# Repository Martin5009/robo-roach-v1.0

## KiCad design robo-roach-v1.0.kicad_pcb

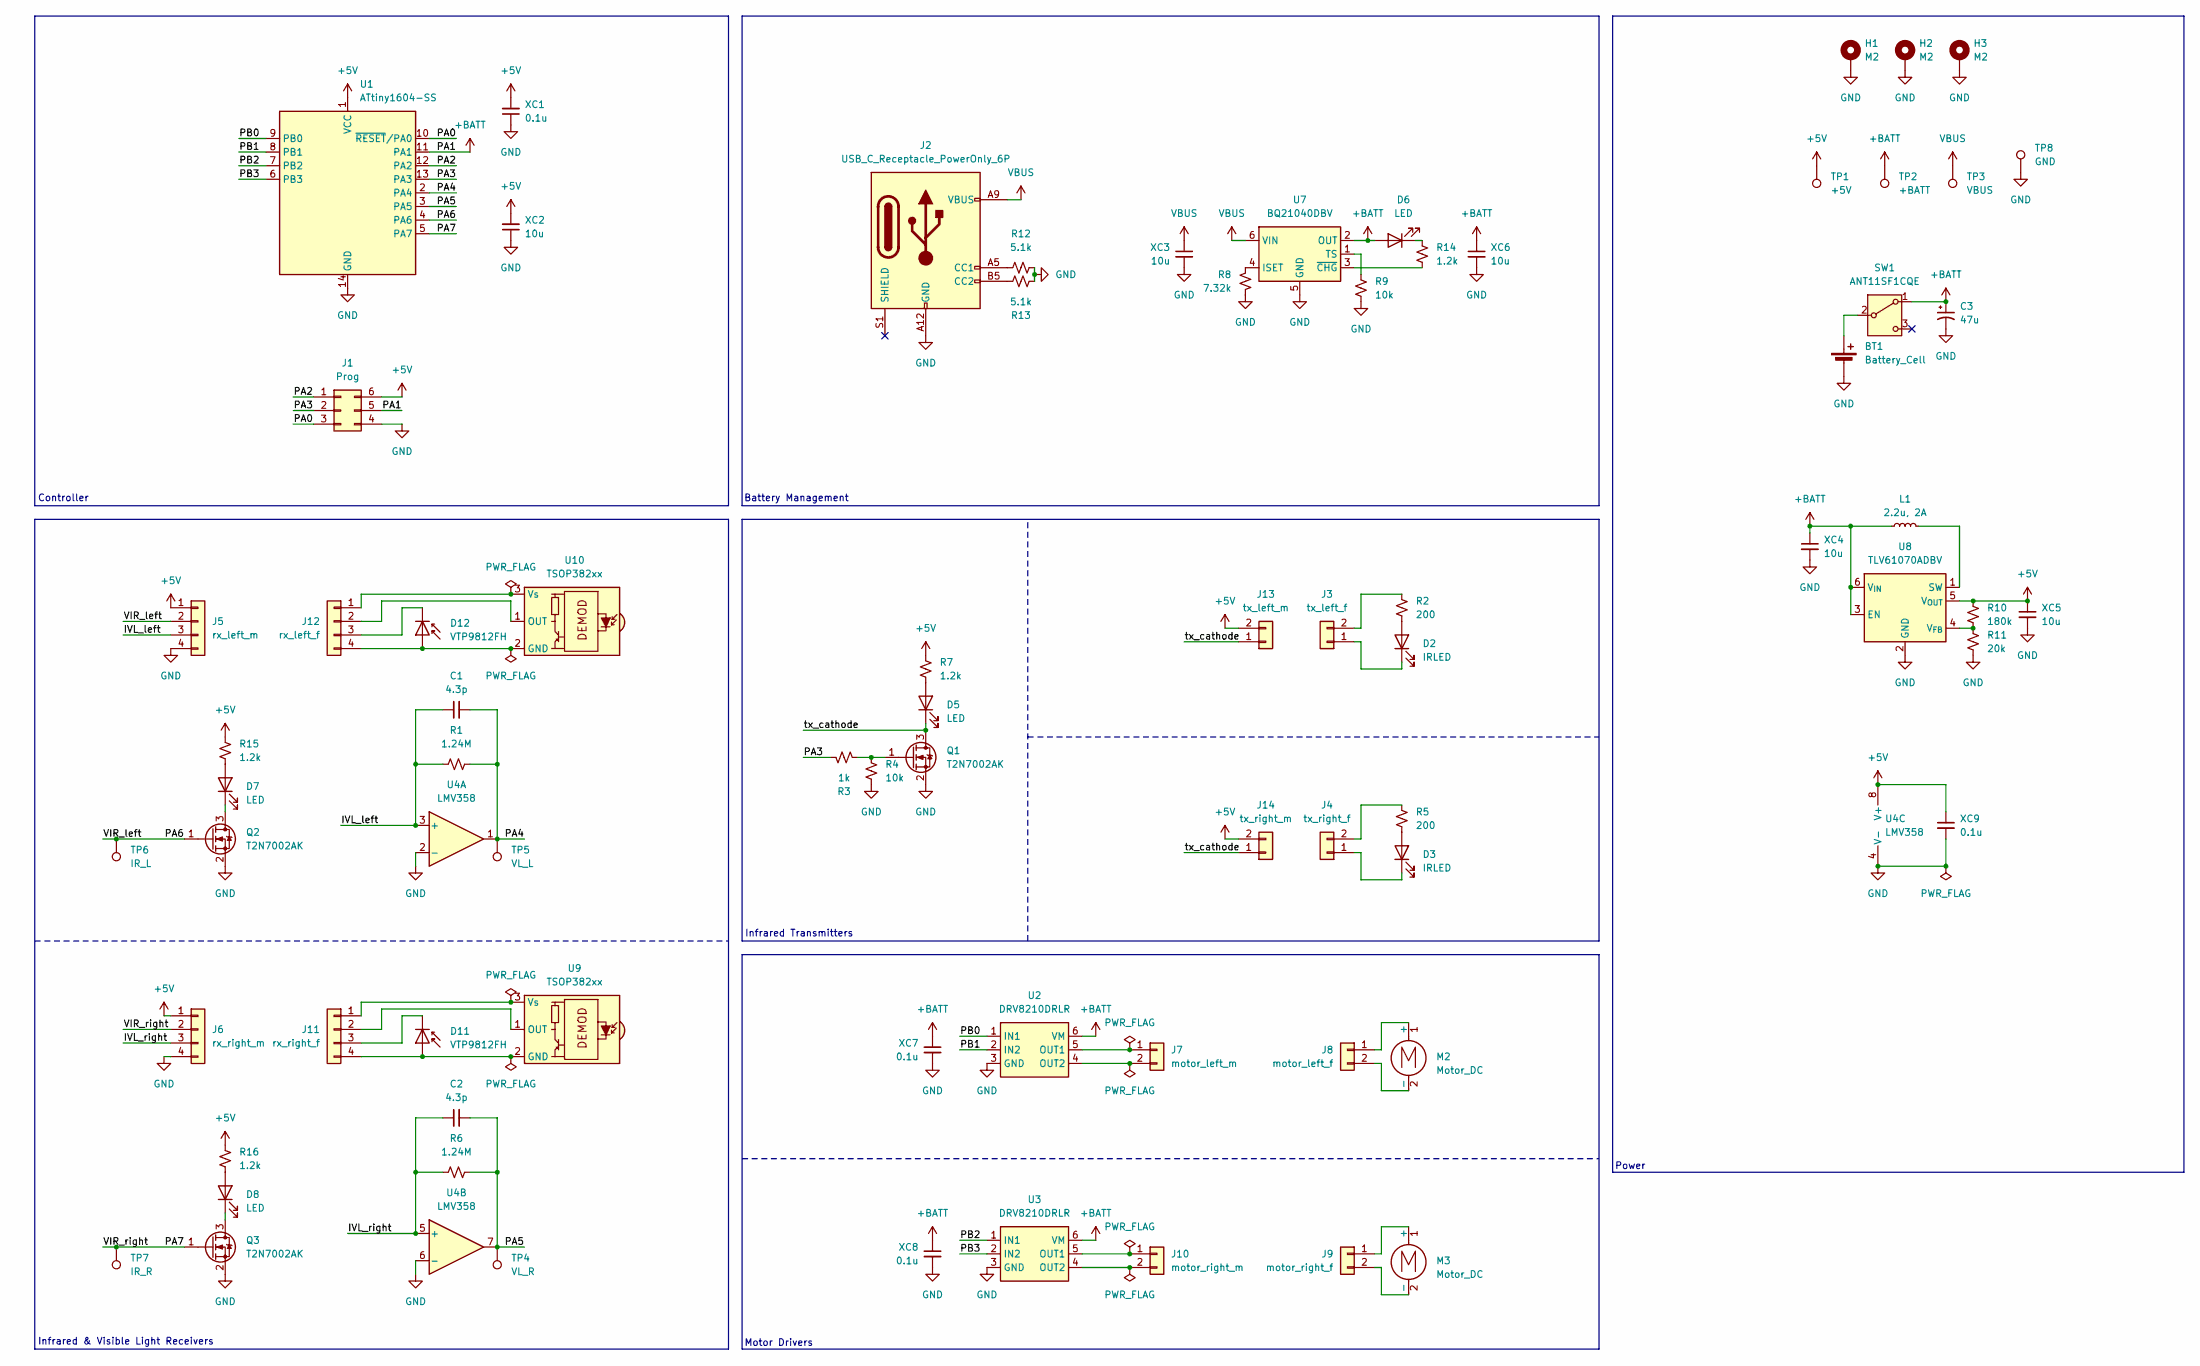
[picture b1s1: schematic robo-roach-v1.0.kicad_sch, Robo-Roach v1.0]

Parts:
BT1: Battery_Cell; LHA-02-TS
C1, C2: 4.3p; C_0603_1608Metric_Pad1.08x0.95mm_HandSolder
C3: 47u; CP_Radial_D5.0mm_P2.00mm
D2, D3: IRLED; LED_D5.0mm
D5, D6, D7, D8: LED; LED_0805_2012Metric_Pad1.15x1.40mm_HandSolder
D11, D12: VTP9812FH; LED_D5.0mm
H1, H2, H3: M2; MountingHole_2.2mm_M2_DIN965_Pad
J1: Prog; SWR204-NRTN-D03-ST-GA
J2: USB_C_Receptacle_PowerOnly_6P; USB_C_Receptacle_HRO_TYPE-C-31-M-17
J3: tx_left_f; LHA-02-TS
J4: tx_right_f; LHA-02-TS
J5: rx_left_m; LHA-04-TS
J6: rx_right_m; LHA-04-TS
J7: motor_left_m; LHA-02-TS
J8: motor_left_f
J9: motor_right_f
J10: motor_right_m; LHA-02-TS
J11: rx_right_f; LHA-04-TS
J12: rx_left_f; LHA-04-TS
J13: tx_left_m; LHA-02-TS
J14: tx_right_m; LHA-02-TS
L1: 2.2u, 2A; L_1008_2520Metric_Pad1.43x2.20mm_HandSolder
M2, M3: Motor_DC
Q1, Q2, Q3: T2N7002AK; SOT-23
R1, R6: 1.24M; R_0603_1608Metric_Pad0.98x0.95mm_HandSolder
R2, R5: 200; R_0603_1608Metric_Pad0.98x0.95mm_HandSolder
R3: 1k; R_0603_1608Metric_Pad0.98x0.95mm_HandSolder
R4, R9: 10k; R_0603_1608Metric_Pad0.98x0.95mm_HandSolder
R7, R14, R15, R16: 1.2k; R_0603_1608Metric_Pad0.98x0.95mm_HandSolder
R8: 7.32k; R_0603_1608Metric_Pad0.98x0.95mm_HandSolder
R10: 180k; R_0603_1608Metric_Pad0.98x0.95mm_HandSolder
R11: 20k; R_0603_1608Metric_Pad0.98x0.95mm_HandSolder
R12, R13: 5.1k; R_0603_1608Metric_Pad0.98x0.95mm_HandSolder
SW1: ANT11SF1CQE; ANT11SECQE
TP1: +5V; TestPoint_THTPad_D1.0mm_Drill0.5mm
TP2: +BATT; TestPoint_THTPad_D1.0mm_Drill0.5mm
TP3: VBUS; TestPoint_THTPad_D1.0mm_Drill0.5mm
TP4: VL_R; TestPoint_THTPad_D1.0mm_Drill0.5mm
TP5: VL_L; TestPoint_THTPad_D1.0mm_Drill0.5mm
TP6: IR_L; TestPoint_THTPad_D1.0mm_Drill0.5mm
TP7: IR_R; TestPoint_THTPad_D1.0mm_Drill0.5mm
TP8: GND; TestPoint_THTPad_D1.0mm_Drill0.5mm
U1: ATtiny1604-SS; SOIC-14_3.9x8.7mm_P1.27mm
U2, U3: DRV8210DRLR; SOT-563
U4: LMV358; VSSOP-8_3x3mm_P0.65mm
U7: BQ21040DBV; SOT-23-6
U8: TLV61070ADBV; SOT-23-6
U9, U10: TSOP382xx; TSOP38336_Right_Angled
XC1, XC7, XC8, XC9: 0.1u; C_0603_1608Metric_Pad1.08x0.95mm_HandSolder
XC2, XC3, XC4, XC5, XC6: 10u; C_0603_1608Metric_Pad1.08x0.95mm_HandSolder

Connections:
+5V: J1.6, J5.1, J6.1, J13.2, J14.2, R7.1, R10.1, R15.1, R16.1, TP1.1, U1.1 (VCC), U4.8 (V+), U8.5 (V_{OUT}), XC1.2, XC2.2, XC5.1, XC9.1
+BATT: C3.1, D6.2 (A), J1.5, L1.1, SW1.1 (A), TP2.1, U1.11 (PA1), U2.6 (VM), U3.6 (VM), U7.2 (OUT), U8.3 (EN), U8.6 (V_{IN}), XC4.1, XC6.1, XC7.1, XC8.1
/IVL_left: C1.1, J5.3, R1.1, U4.3 (+)
/IVL_right: C2.1, J6.3, R6.1, U4.5 (+)
/PA0: J1.3, U1.10 (~RESET/PA0)
/PA2: J1.1, U1.12 (PA2)
/PA3: J1.2, R3.1, U1.13 (PA3)
/PA4: C1.2, R1.2, TP5.1, U1.2 (PA4), U4.1
/PA5: C2.2, R6.2, TP4.1, U1.3 (PA5), U4.7
/PA6: J5.2, Q2.1 (G), TP6.1, U1.4 (PA6)
/PA7: J6.2, Q3.1 (G), TP7.1, U1.5 (PA7)
/PB0: U1.9 (PB0), U2.1 (IN1)
/PB1: U1.8 (PB1), U2.2 (IN2)
/PB2: U1.7 (PB2), U3.1 (IN1)
/PB3: U1.6 (PB3), U3.2 (IN2)
/tx_cathode: D5.1 (K), J13.1, J14.1, Q1.3 (D)
GND: BT1.2 (-), C3.2, H1.1, H2.1, H3.1, J1.4, J2.A12 (GND), J2.B12 (GND), J5.4, J6.4, Q1.2 (S), Q2.2 (S), Q3.2 (S), R4.2, R8.2, R9.1, R11.2, R12.2, R13.1, TP8.1, U1.14 (GND), U2.3 (GND), U3.3 (GND), U4.2 (-), U4.4 (V-), U4.6 (-), U7.5 (GND), U8.2 (GND), XC1.1, XC2.1, XC3.2, XC4.2, XC5.2, XC6.2, XC7.2, XC8.2, XC9.2
unnamed: BT1.1 (+), SW1.2 (B)
unnamed: D2.2 (A), R2.2
unnamed: D2.1 (K), J3.1
unnamed: D3.2 (A), R5.2
unnamed: D3.1 (K), J4.1
unnamed: D5.2 (A), R7.2
unnamed: D6.1 (K), R14.2
unnamed: D7.2 (A), R15.2
unnamed: D7.1 (K), Q2.3 (D)
unnamed: D8.2 (A), R16.2
unnamed: D8.1 (K), Q3.3 (D)
unnamed: D11.2 (A), J11.4, U9.2 (GND)
unnamed: D11.1 (K), J11.3
unnamed: D12.2 (A), J12.4, U10.2 (GND)
unnamed: D12.1 (K), J12.3
unnamed: J2.A5 (CC1), R12.1
unnamed: J2.B5 (CC2), R13.2
unnamed: J3.2, R2.1
unnamed: J4.2, R5.1
unnamed: J7.1, U2.5 (OUT1)
unnamed: J7.2, U2.4 (OUT2)
unnamed: J8.1, M2.1 (+)
unnamed: J8.2, M2.2 (-)
unnamed: J9.1, M3.1 (+)
unnamed: J9.2, M3.2 (-)
unnamed: J10.1, U3.5 (OUT1)
unnamed: J10.2, U3.4 (OUT2)
unnamed: J11.1, U9.3 (Vs)
unnamed: J11.2, U9.1 (OUT)
unnamed: J12.1, U10.3 (Vs)
unnamed: J12.2, U10.1 (OUT)
unnamed: Q1.1 (G), R3.2, R4.1
unnamed: R8.1, U7.4 (ISET)
unnamed: R9.2, U7.1 (TS)
unnamed: R14.1, U7.3 (~CHG)
unnamed: L1.2, U8.1 (SW)
unnamed: R10.2, R11.1, U8.4 (V_{FB})
VBUS: J2.A9 (VBUS), J2.B9 (VBUS), TP3.1, U7.6 (VIN), XC3.1

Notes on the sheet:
Controller
Infrared & Visible Light Receivers
Battery Management
Power
Infrared Transmitters
Motor Drivers

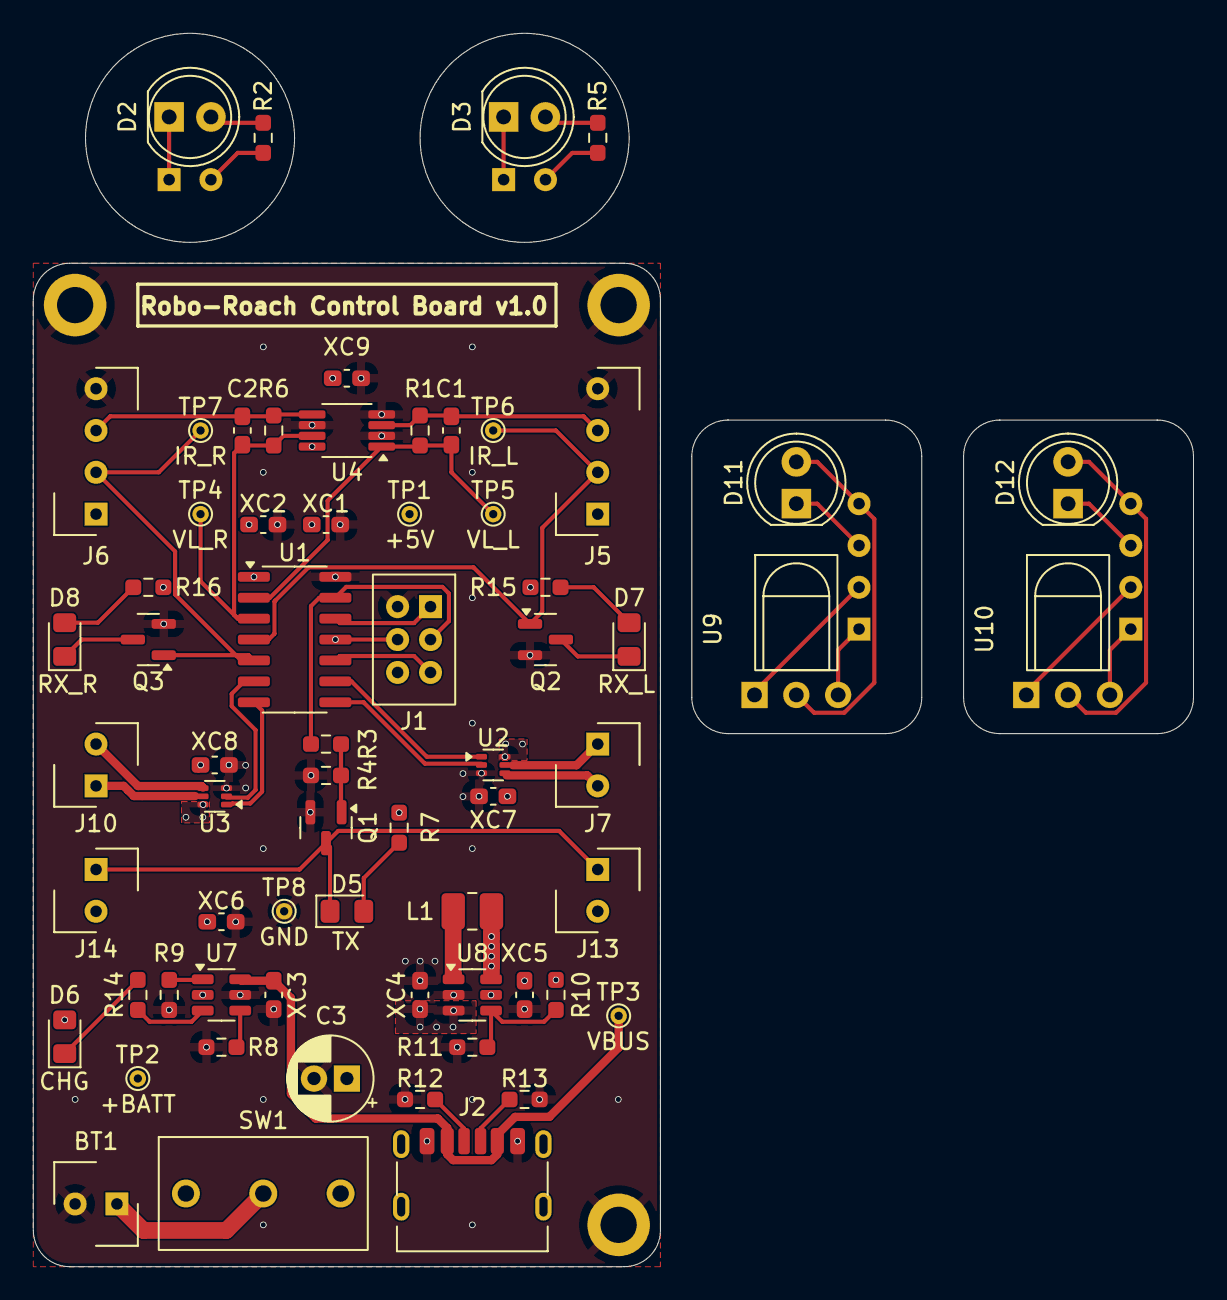
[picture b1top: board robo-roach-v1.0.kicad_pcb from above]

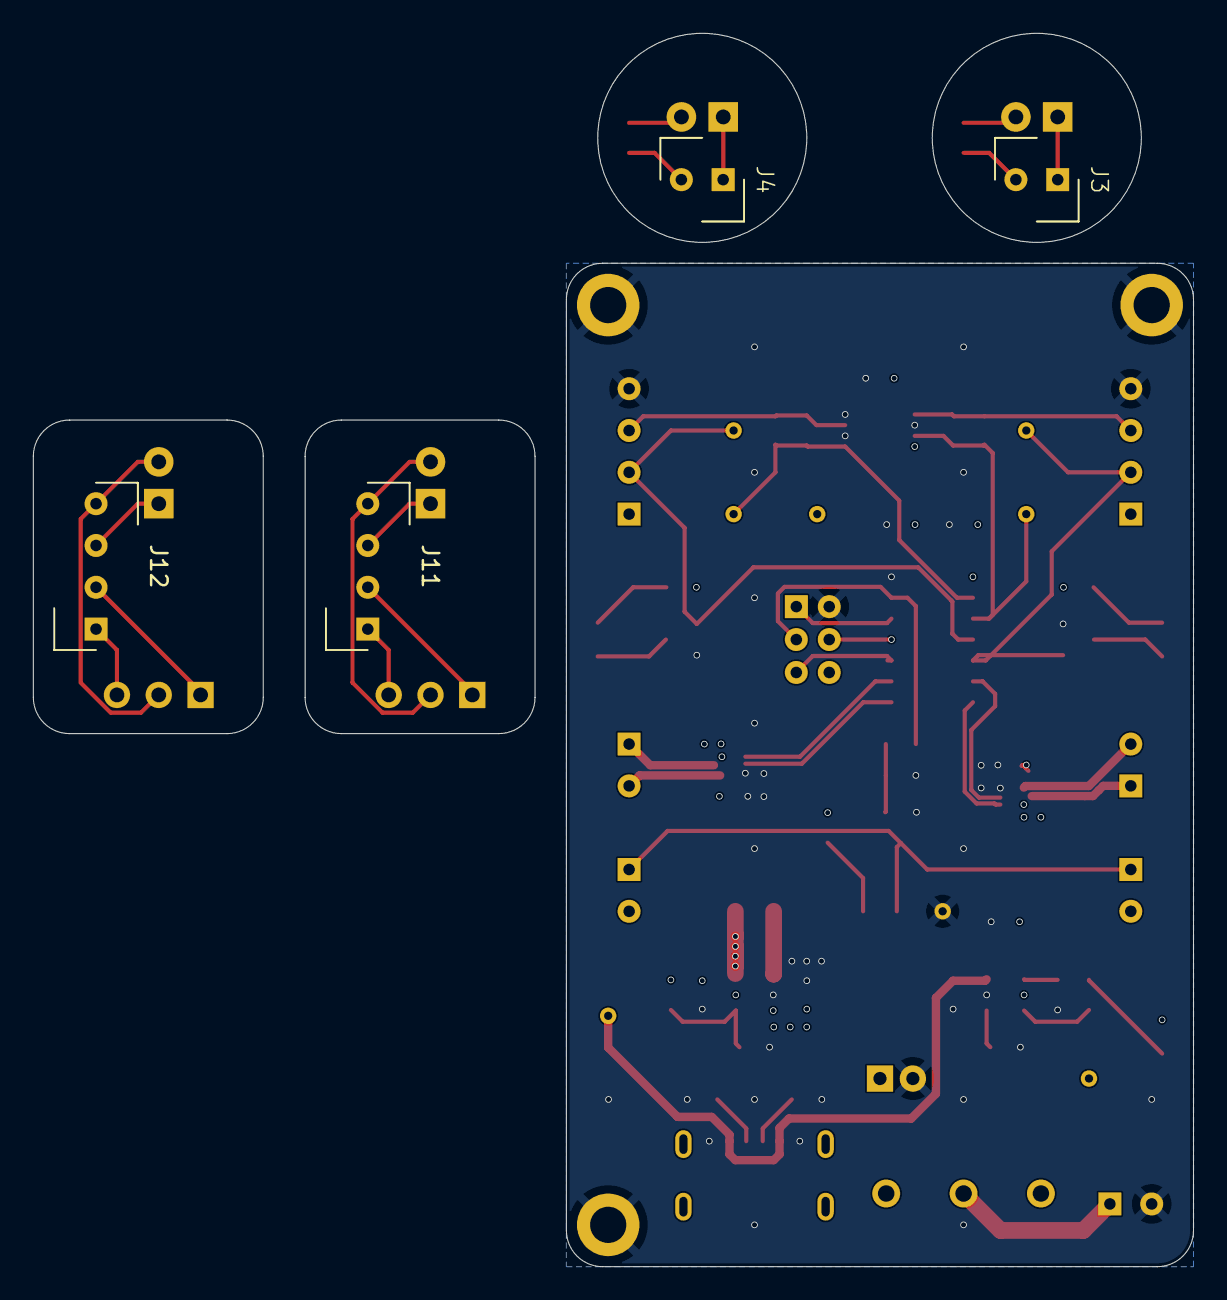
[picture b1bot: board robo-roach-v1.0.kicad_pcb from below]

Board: 4 copper layers, 70.5 x 74.9 mm, 73 parts (4 on the bottom side), 51 nets.

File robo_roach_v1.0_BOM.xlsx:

Id | Designator | Footprint | Quantity | Comment | Supplier and ref | Column1 | _1
1 | R15,R16,R14,R7 | 0603 | 4 | 1.2k
2 | R10 | 0603 | 1 | 180k
3 | D6,D8,D5,D7 | 0805 | 4 | LED
5 | XC5,XC3,XC2,XC4,XC6 | 0603 | 5 | 10u
6 | R12,R13 | 0603 | 2 | 5.1k
7 | XC9,XC1,XC8,XC7 | 0603 | 4 | 0.1u
8 | SW1 | ANT11SECQE | 1 | ANT11SF1CQE
12 | C2,C1 | 0603 | 2 | 4.3p
13 | J1 | SWR204-NRTN-D03-ST-GA | 1 | Prog
14 | C3 | CP_Radial_D5.0mm_P2.00mm | 1 | 47u
15 | Q2,Q3,Q1 | SOT-23 | 3 | T2N7002AK
16 | R4,R9 | 0603 | 2 | 10k
17 | U1 | SOIC-14_3.9x8.7mm_P1.27mm | 1 | ATtiny1604-SS
19 | U3,U2 | SOT-563 | 2 | DRV8210DRLR
20 | U7 | SOT-23-6 | 1 | BQ21040DBV
21 | R6,R1 | 0603 | 2 | 1.24M
22 | R11 | 0603 | 1 | 20k
24 | R3 | 0603 | 1 | 1k
25 | U8 | SOT-23-6 | 1 | TLV61070ADBV
29 | U4 | VSSOP-8_3x3mm_P0.65mm | 1 | LMV358
30 | J2 | USB_C_Receptacle_HRO_TYPE-C-31-M-17 | 1 | USB_C_Receptacle_PowerOnly_6P
31 | R8 | 0603 | 1 | 7.32k
34 | L1 | 1008 | 1 | 2.2u, 2A
